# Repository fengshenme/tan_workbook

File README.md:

# 整理.各种练习代码

- Android相关

- c与c++,linux c

- java spring springboot springmvc resultapi风格web接口, 问题修复中。。

- Python 练习demo

- s下都是电子相关

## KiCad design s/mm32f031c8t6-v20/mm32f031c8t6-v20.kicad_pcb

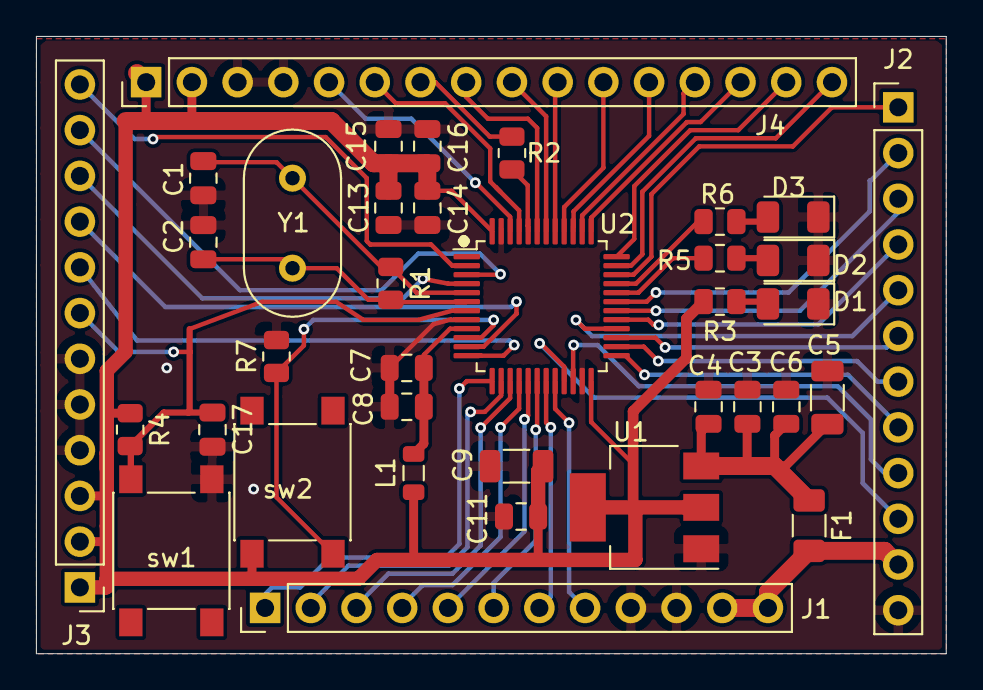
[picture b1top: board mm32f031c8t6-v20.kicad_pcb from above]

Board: 2 copper layers, 50.5 x 34.3 mm, 36 parts (0 on the bottom side), 50 nets.

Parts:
C1, C2: 20pf; C_0805_2012Metric
C3, C7, C13, C15: 1uF; C_0805_2012Metric
C4, C8, C14, C16: 10nF; C_0805_2012Metric
C5, C9: 10uf; C_1206_3216Metric
C6, C11, C17: 100nf; C_0805_2012Metric
D1, D2, D3: LED; LED_1206_3216Metric
F1: Polyfuse; Fuse_1206_3216Metric
J1, J2, J3: Conn_01x12; PinHeader_1x12_P2.54mm_Vertical
J4: Conn_01x16; PinHeader_1x16_P2.54mm_Vertical
L1: 3.3uH; L_0805_2012Metric
R1: 1m; R_0805_2012Metric
R2, R4, R7: 10k; R_0805_2012Metric
R3, R5, R6: 1k; R_0805_2012Metric
U1: MyAMS1117-3.3V; SOT-223
U2: MM32F031C8T6; LQFP-48_7x7mm_P0.5mm
Y1: 8m; Resonator-2Pin_W10.0mm_H5.0mm
sw1, sw2: switch_4p1t; SW_Push_1P1T_NO_6x6mm_H9.5mm

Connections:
+5V: C3.1, C4.1, C5.1, C6.1, F1.1, U1.3
/3V3: C9.1, C11.1, C13.1, C14.1, C15.1, C16.1, J3.1, J3.2, J3.3, J4.1, J4.2, L1.1, R3.2, R4.1, U1.2, U1.4, U2.24, U2.48, sw2.1
/BOOT0: R2.2, U2.44
/NRST: C17.1, J3.7, R4.2, U2.7, sw1.3
/OSC32_IN: J3.11, U2.3
/OSC32_OUT: J3.10, U2.4
/OSC_IN: C1.1, R1.1, U2.5, Y1.1
/OSC_OUT: C2.1, R1.2, U2.6, Y1.2
/PA0_WAKEUP: R7.1, U2.10, sw2.3
/PA1: J3.9, U2.11
/PA2: J3.8, U2.12
/PA3: J1.1, U2.13
/PA4: J1.2, U2.14
/PA5: J1.3, U2.15
/PA6: J1.4, U2.16
/PA7: J1.5, U2.17
/PA8: J2.4, U2.29
/PA9: J2.3, U2.30
/PA10: J2.2, U2.31
/PA11: R5.2, U2.32
/PA12: R6.2, U2.33
/PA15: J4.13, U2.38
/PB0: J1.6, U2.18
/PB1: J1.7, U2.19
/PB2: J1.8, U2.20
/PB3: J4.12, U2.39
/PB4: J4.11, U2.40
/PB5: J4.10, U2.41
/PB6: J4.9, U2.42
/PB7: J4.8, U2.43
/PB8: J4.6, U2.45
/PB9: J4.5, U2.46
/PB10: J2.10, U2.21
/PB11: J2.9, U2.22
/PB12: J2.8, U2.25
/PB13: J2.7, U2.26
/PB14: J2.6, U2.27
/PB15: J2.5, U2.28
/PC13_TAMPER_RTC: J3.12, U2.2
/PD2: J4.16, U2.35
/PD3: J4.15, U2.36
/SWCLK: J4.14, U2.37
/SWDIO: J2.1, U2.34
/VDDA: C7.1, C8.1, L1.2, U2.9
/in5V: F1.2, J1.11, J1.12, J2.11
GND: C1.2, C2.2, C3.2, C4.2, C5.2, C6.2, C7.2, C8.2, C9.2, C11.2, C13.2, C14.2, C15.2, C16.2, C17.2, D1.1, D2.1, D3.1, J1.9, J1.10, J2.12, J3.4, J3.5, J3.6, J4.3, J4.4, R7.2, U1.1, U2.8, U2.23, U2.47, sw1.1
unnamed: D1.2, R3.1
unnamed: D2.2, R5.1
unnamed: D3.2, R6.1
unnamed: J4.7, R2.1

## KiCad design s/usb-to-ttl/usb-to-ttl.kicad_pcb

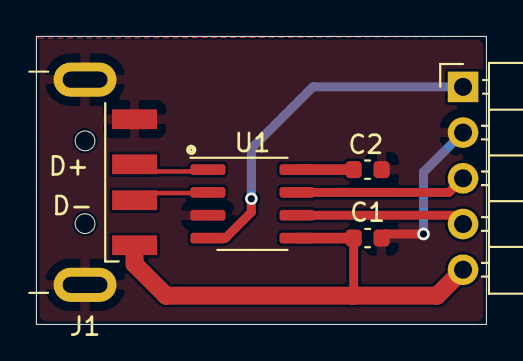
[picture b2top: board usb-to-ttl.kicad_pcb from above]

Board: 2 copper layers, 25.0 x 16.0 mm, 5 parts (0 on the bottom side), 8 nets.

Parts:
C1, C2: 104; C_0603_1608Metric
J1: USB_A; USB_A_CNCTech_1001-011-01101_Horizontal
J2: Conn_01x05; PinHeader_1x05_P2.54mm_Horizontal
U1: CH330N; SOIC-8_3.9x4.9mm_P1.27mm

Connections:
+5V: C1.1, J1.1, J2.5, U1.5
/D+: J1.3, U1.1
/D-: J1.2, U1.2
/RTS: J2.1, U1.4
/RXD: J2.3, U1.7
/TXD: J2.4, U1.6
/V3: C2.1, U1.8
GND: C1.2, C2.2, J1.4, J1.5, J2.2, U1.3

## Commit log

2019-09-12 Delete java.md
    改
2019-09-14 添加一个爬虫分词微服务
    我这爬取的是csdn的文章简介,用来分类训练
2019-10-03 持久层用mybatis,优化了下数据库字段
    这样一个ssh和ssm就其了
2019-10-31 添加一个文件微服务
    添加一个文件微服务
    一个简单的图片微服务,视频微服务,文件微服务
    Add a file microservice
    A simple picture micro service, video micro service, file micro service
2019-10-31 增加一个文件服务
2019-11-11 数据提取,导入导出,修改优化下
2019-11-11 日常更新
2019-11-13 导出csv
2019-11-14 更新2.2.1
2019-11-17 增加了批量插入
2019-11-17 就这样了
2019-11-20 日常维修bug
2019-11-23 增加,休息了明天再弄
2019-11-23 jiayi
2019-11-23 jiaer
2019-12-07 更新,模型训练改为python
2019-12-15 天天修bug
2019-12-16 合并更新
2019-12-17 发现bug,修复一下
2019-12-20 更新配置
2019-12-20 修改首页轮播
2019-12-25 后端更新响应方式,前端更新vuex
2019-12-25 增加lombok
2019-12-29 后端更改将entity接收改为jsonobject,前端更新评论组件
2020-01-05 后端添加响应,优化下sql语句,前端添加请求响应拦截
2020-01-11 更新mapper
2020-01-12 修改下id生成
2020-01-19 更新一下mapper,更新web
2020-01-31 增加更新，crud基本完成
2020-04-05 Bump acorn from 6.3.0 to 6.4.1 in /vueWeb
    Bumps [acorn](https://github.com/acornjs/acorn) from 6.3.0 to 6.4.1.
    - [Release notes](https://github.com/acornjs/acorn/releases)
    - [Commits](https://github.com/acornjs/acorn/compare/6.3.0...6.4.1)
2020-05-02 更新main布局
2020-05-02 提示升级
2020-06-07 Bump websocket-extensions from 0.1.3 to 0.1.4 in /vueWeb
    Bumps [websocket-extensions](https://github.com/faye/websocket-extensions-node) from 0.1.3 to 0.1.4.
    - [Release notes](https://github.com/faye/websocket-extensions-node/releases)
    - [Changelog](https://github.com/faye/websocket-extensions-node/blob/master/CHANGELOG.md)
    - [Commits](https://github.com/faye/websocket-extensions-node/compare/0.1.3...0.1.4)
2020-07-19 Bump lodash from 4.17.15 to 4.17.19 in /vueWeb
    Bumps [lodash](https://github.com/lodash/lodash) from 4.17.15 to 4.17.19.
    - [Release notes](https://github.com/lodash/lodash/releases)
    - [Commits](https://github.com/lodash/lodash/compare/4.17.15...4.17.19)
2020-08-01 Bump elliptic from 6.5.2 to 6.5.3 in /vueWeb
    Bumps [elliptic](https://github.com/indutny/elliptic) from 6.5.2 to 6.5.3.
    - [Release notes](https://github.com/indutny/elliptic/releases)
    - [Commits](https://github.com/indutny/elliptic/compare/v6.5.2...v6.5.3)
2020-09-05 Bump @hapi/hoek from 8.5.0 to 8.5.1 in /vueWeb
    Bumps [@hapi/hoek](https://github.com/hapijs/hoek) from 8.5.0 to 8.5.1.
    - [Release notes](https://github.com/hapijs/hoek/releases)
    - [Commits](https://github.com/hapijs/hoek/compare/v8.5.0...v8.5.1)
2020-09-10 Bump http-proxy from 1.18.0 to 1.18.1 in /vueWeb
    Bumps [http-proxy](https://github.com/http-party/node-http-proxy) from 1.18.0 to 1.18.1.
    - [Release notes](https://github.com/http-party/node-http-proxy/releases)
    - [Changelog](https://github.com/http-party/node-http-proxy/blob/master/CHANGELOG.md)
    - [Commits](https://github.com/http-party/node-http-proxy/compare/1.18.0...1.18.1)
2020-11-04 清理角标
2020-11-06 更新c文件夹
2020-11-11 无用的.out文件删除
2020-11-16 无用 删除
2020-12-20 更换IDE测试
2021-01-27 null
2021-01-27 rename
2021-01-27 更正目录
2021-01-27 stm32 test
2021-01-27 clear
2021-01-28 串口调试工具
2021-02-22 add usb-to-ttl pcb
2021-02-22 串口蓝牙调试
2021-02-22 update ignore
2021-03-04 差分线 等长 等宽
2021-03-04 降低耗电
2021-03-12 更新学习板
2021-03-14 更新自述
2021-04-26 Bump commons-io from 2.6 to 2.7 in /java/fileshen
    Bumps commons-io from 2.6 to 2.7.
2021-08-23 Bump jsoup from 1.12.1 to 1.14.2 in /java/fileshen
    Bumps [jsoup](https://github.com/jhy/jsoup) from 1.12.1 to 1.14.2.
    - [Release notes](https://github.com/jhy/jsoup/releases)
    - [Changelog](https://github.com/jhy/jsoup/blob/master/CHANGES)
    - [Commits](https://github.com/jhy/jsoup/compare/jsoup-1.12.1...jsoup-1.14.2)
    ---
    updated-dependencies:
2021-09-04 添加笔记
2021-09-04 添加笔记改
2021-10-01 无用清除
2021-10-01 del .ipynb* folder
2022-01-26 del ...
2022-01-26 test ...
2022-01-26 test update
2022-03-09 更新git
2022-03-31 Bump spring-boot-starter-web in /java/webdemoa
    Bumps [spring-boot-starter-web](https://github.com/spring-projects/spring-boot) from 2.3.6.RELEASE to 2.5.12.
    - [Release notes](https://github.com/spring-projects/spring-boot/releases)
    - [Commits](https://github.com/spring-projects/spring-boot/compare/v2.3.6.RELEASE...v2.5.12)
    ---
    updated-dependencies:
    - dependency-name: org.springframework.boot:spring-boot-starter-web
2022-03-31 Bump spring-boot-starter-web in /java/fileshen
    Bumps [spring-boot-starter-web](https://github.com/spring-projects/spring-boot) from 2.1.3.RELEASE to 2.5.12.
    - [Release notes](https://github.com/spring-projects/spring-boot/releases)
    - [Commits](https://github.com/spring-projects/spring-boot/compare/v2.1.3.RELEASE...v2.5.12)
    ---
    updated-dependencies:
    - dependency-name: org.springframework.boot:spring-boot-starter-web
2022-06-17 Bump fastjson from 1.2.62 to 1.2.83 in /java/fileshen
    Bumps [fastjson](https://github.com/alibaba/fastjson) from 1.2.62 to 1.2.83.
    - [Release notes](https://github.com/alibaba/fastjson/releases)
    - [Commits](https://github.com/alibaba/fastjson/compare/1.2.62...1.2.83)
    ---
    updated-dependencies:
    - dependency-name: com.alibaba:fastjson
2022-06-21 Bump mysql-connector-java from 8.0.16 to 8.0.28 in /java/webdemoa
    Bumps [mysql-connector-java](https://github.com/mysql/mysql-connector-j) from 8.0.16 to 8.0.28.
    - [Release notes](https://github.com/mysql/mysql-connector-j/releases)
    - [Changelog](https://github.com/mysql/mysql-connector-j/blob/release/8.0/CHANGES)
    - [Commits](https://github.com/mysql/mysql-connector-j/compare/8.0.16...8.0.28)
    ---
    updated-dependencies:
2022-06-21 Bump mysql-connector-java from 8.0.16 to 8.0.28 in /java/fileshen
    Bumps [mysql-connector-java](https://github.com/mysql/mysql-connector-j) from 8.0.16 to 8.0.28.
    - [Release notes](https://github.com/mysql/mysql-connector-j/releases)
    - [Changelog](https://github.com/mysql/mysql-connector-j/blob/release/8.0/CHANGES)
    - [Commits](https://github.com/mysql/mysql-connector-j/compare/8.0.16...8.0.28)
    ---
    updated-dependencies:
2022-09-01 Bump jsoup from 1.12.1 to 1.15.3 in /java/fileshen
    Bumps [jsoup](https://github.com/jhy/jsoup) from 1.12.1 to 1.15.3.
    - [Release notes](https://github.com/jhy/jsoup/releases)
    - [Changelog](https://github.com/jhy/jsoup/blob/master/CHANGES)
    - [Commits](https://github.com/jhy/jsoup/compare/jsoup-1.12.1...jsoup-1.15.3)
    ---
    updated-dependencies:
2023-08-28 Update .gitignore
    更新下
2023-08-28 tk 串口界面
    一页简单
2024-10-03 Bump commons-io:commons-io from 2.6 to 2.14.0 in /java/fileshen
    Bumps commons-io:commons-io from 2.6 to 2.14.0.
    ---
    updated-dependencies:
    - dependency-name: commons-io:commons-io
    dependency-type: direct:production
    ...
